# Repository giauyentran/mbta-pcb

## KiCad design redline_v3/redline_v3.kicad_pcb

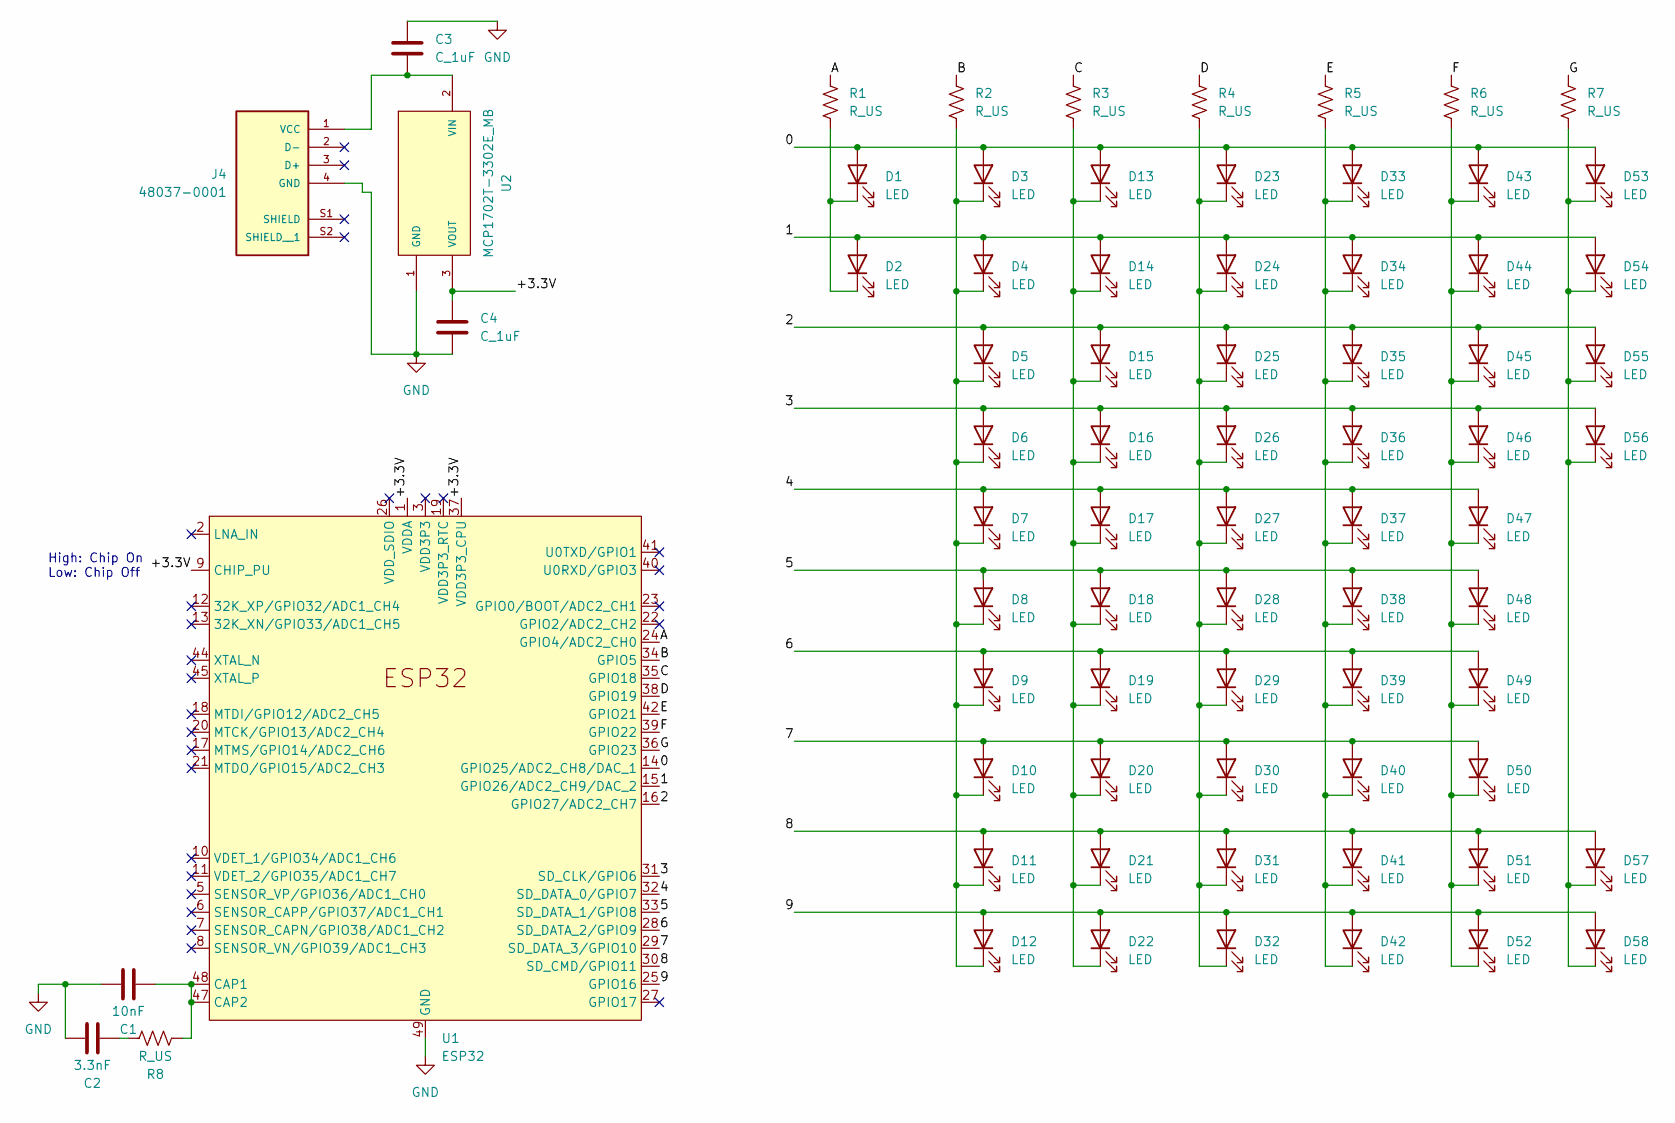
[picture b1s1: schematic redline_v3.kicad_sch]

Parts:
C1: 10nF; C_0603_1608Metric
C2: 3.3nF; C_0603_1608Metric
C3, C4: C_1uF; C_0603_1608Metric; MPN 1276-6470-1-ND
D1, D2, D3, D4, D5, D6, D7, D8, D9, D10, D11, D12, D13, D14, D15, D16, D17, D18, D19, D20, D21, D22, D23, D24, D25, D26, D27, D28, D29, D30, D31, D32, D33, D34, D35, D36, D37, D38, D39, D40, D41, D42, D43, D44, D45, D46, D47, D48, D49, D50, D51, D52, D53, D54, D55, D56, D57, D58: LED; LED_0603_1608Metric
J4: 48037-0001; MOLEX_USB_conn; PARTREV D
R1, R2, R3, R4, R5, R6, R7, R8: R_US; R_0603_1608Metric
U1: ESP32; QFN-48-1EP_8x8mm_P0.5mm_EP6.2x6.2mm
U2: MCP1702T-3302E_MB; MCP1702T; PARTREV E

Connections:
/0: D1.2 (A), D3.2 (A), D13.2 (A), D23.2 (A), D33.2 (A), D43.2 (A), D53.2 (A), U1.14 (GPIO25/ADC2_CH8/DAC_1)
/1: D2.2 (A), D4.2 (A), D14.2 (A), D24.2 (A), D34.2 (A), D44.2 (A), D54.2 (A), U1.15 (GPIO26/ADC2_CH9/DAC_2)
/2: D5.2 (A), D15.2 (A), D25.2 (A), D35.2 (A), D45.2 (A), D55.2 (A), U1.16 (GPIO27/ADC2_CH7)
/3: D6.2 (A), D16.2 (A), D26.2 (A), D36.2 (A), D46.2 (A), D56.2 (A), U1.31 (SD_CLK/GPIO6)
/4: D7.2 (A), D17.2 (A), D27.2 (A), D37.2 (A), D47.2 (A), U1.32 (SD_DATA_0/GPIO7)
/5: D8.2 (A), D18.2 (A), D28.2 (A), D38.2 (A), D48.2 (A), U1.33 (SD_DATA_1/GPIO8)
/6: D9.2 (A), D19.2 (A), D29.2 (A), D39.2 (A), D49.2 (A), U1.28 (SD_DATA_2/GPIO9)
/7: D10.2 (A), D20.2 (A), D30.2 (A), D40.2 (A), D50.2 (A), U1.29 (SD_DATA_3/GPIO10)
/8: D11.2 (A), D21.2 (A), D31.2 (A), D41.2 (A), D51.2 (A), D57.2 (A), U1.30 (SD_CMD/GPIO11)
/9: D12.2 (A), D22.2 (A), D32.2 (A), D42.2 (A), D52.2 (A), D58.2 (A), U1.25 (GPIO16)
/+3.3V: C4.1, U1.1 (VDDA), U1.9 (CHIP_PU), U1.37 (VDD3P3_CPU), U1.43 (VDDA), U1.46 (VDDA), U2.3 (VOUT)
/A: R1.1, U1.24 (GPIO4/ADC2_CH0)
/B: R2.1, U1.34 (GPIO5)
/C: R3.1, U1.35 (GPIO18)
/D: R4.1, U1.38 (GPIO19)
/E: R5.1, U1.42 (GPIO21)
/F: R6.1, U1.39 (GPIO22)
/G: R7.1, U1.36 (GPIO23)
GND: C1.2, C2.1, C3.2, C4.2, J4.4 (GND), U1.49 (GND), U2.1 (GND)
unnamed: C2.2, R8.1
unnamed: D1.1 (K), D2.1 (K), R1.2
unnamed: D3.1 (K), D4.1 (K), D5.1 (K), D6.1 (K), D7.1 (K), D8.1 (K), D9.1 (K), D10.1 (K), D11.1 (K), D12.1 (K), R2.2
unnamed: D13.1 (K), D14.1 (K), D15.1 (K), D16.1 (K), D17.1 (K), D18.1 (K), D19.1 (K), D20.1 (K), D21.1 (K), D22.1 (K), R3.2
unnamed: D23.1 (K), D24.1 (K), D25.1 (K), D26.1 (K), D27.1 (K), D28.1 (K), D29.1 (K), D30.1 (K), D31.1 (K), D32.1 (K), R4.2
unnamed: D33.1 (K), D34.1 (K), D35.1 (K), D36.1 (K), D37.1 (K), D38.1 (K), D39.1 (K), D40.1 (K), D41.1 (K), D42.1 (K), R5.2
unnamed: D43.1 (K), D44.1 (K), D45.1 (K), D46.1 (K), D47.1 (K), D48.1 (K), D49.1 (K), D50.1 (K), D51.1 (K), D52.1 (K), R6.2
unnamed: D53.1 (K), D54.1 (K), D55.1 (K), D56.1 (K), D57.1 (K), D58.1 (K), R7.2
unnamed: C3.1, J4.1 (VCC), U2.2 (VIN)
unnamed: C1.1, R8.2, U1.47 (CAP2), U1.48 (CAP1)

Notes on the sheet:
High: Chip On Low: Chip Off

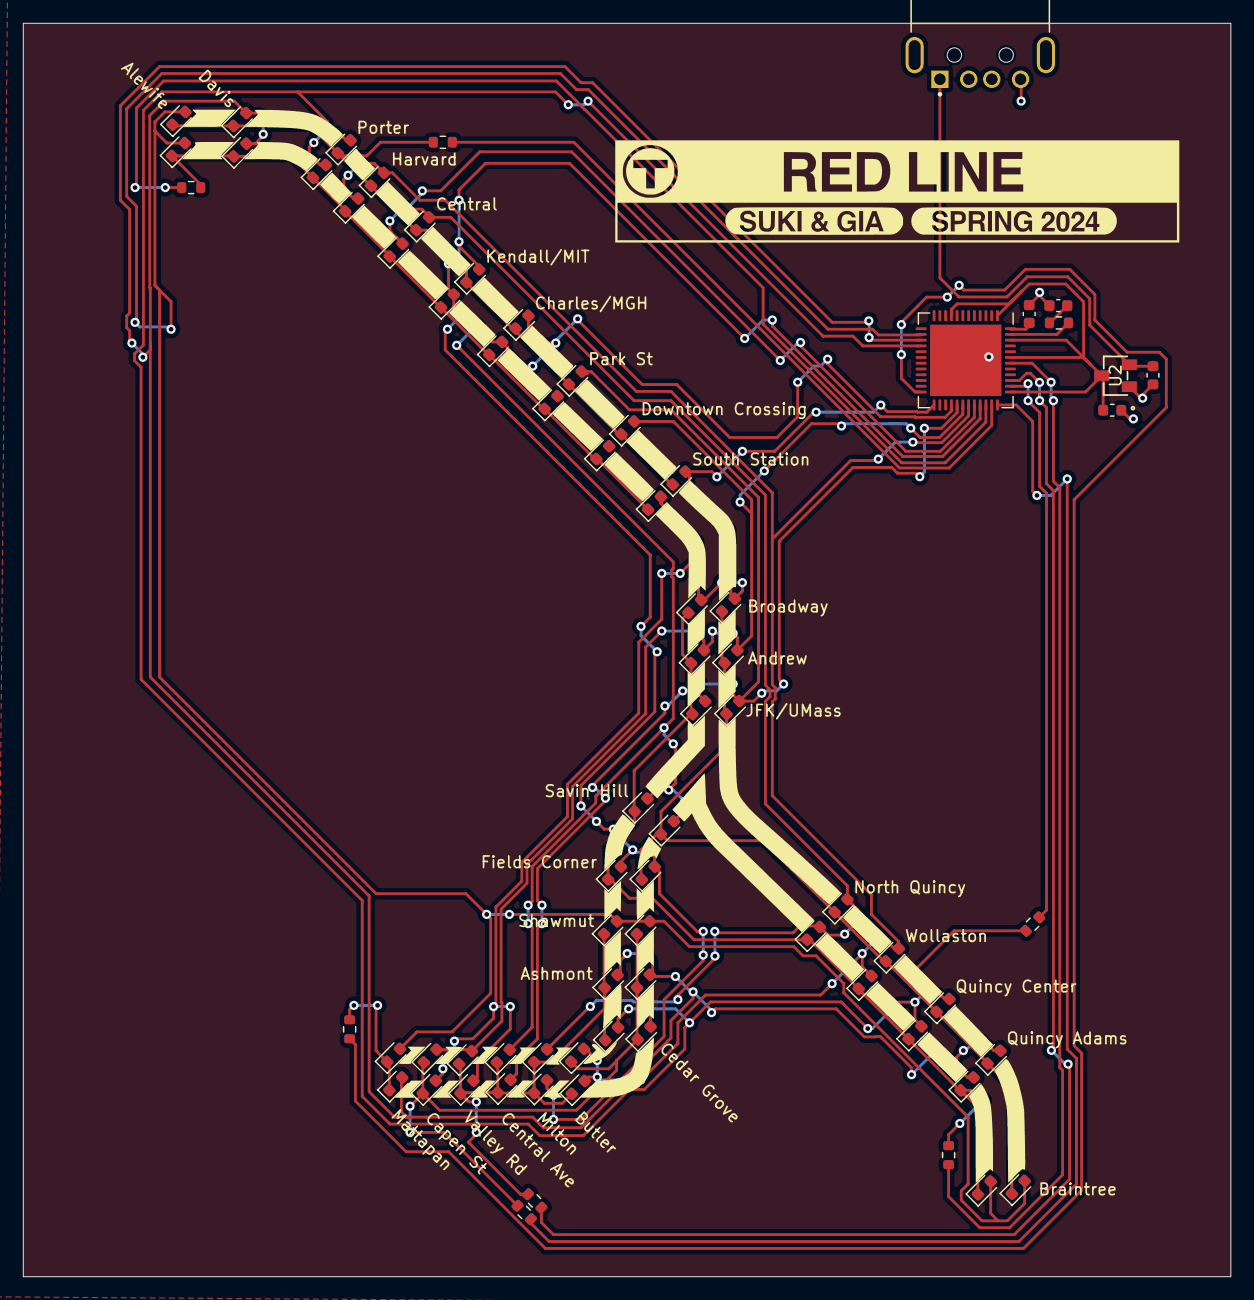
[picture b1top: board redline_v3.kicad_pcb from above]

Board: 2 copper layers, 104.8 x 108.8 mm, 73 parts (0 on the bottom side), 29 nets.

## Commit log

2024-04-23 Started KiCad schematic
2024-04-28 add multiplex speed testing
2024-04-29 create silkscreen graphic
2024-04-29 Completed baseline layout of V2
2024-04-29 Added station labels
2024-04-29 V3 with Gia layout
2024-05-10 remove old silkscreen
2024-05-10 create silkscreen footprint
2024-05-10 add silkscreen
2024-05-10 fix led locations
2024-05-10 add mbta sign
2024-05-10 add silkscreen bitmap
2024-05-11 traces all done
2024-05-11 add station names
